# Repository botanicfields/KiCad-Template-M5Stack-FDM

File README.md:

# KiCad-Template-M5Stack-FDM
a PCB template of FDM-modules of M5Stack with footprints for KiCad.
## for KiCad 6
https://github.com/botanicfields/KiCad6-Environment

## for KiCad 5
- FDM: Fused Deposition Modeling
- Manufacture with a thickness of 1.0 mm.
- M-BUS pin numbers match pin headers and pin sockets in the KiCad library.
- The template has a notch, but it may be actually needed only for the M5Stack controller board.

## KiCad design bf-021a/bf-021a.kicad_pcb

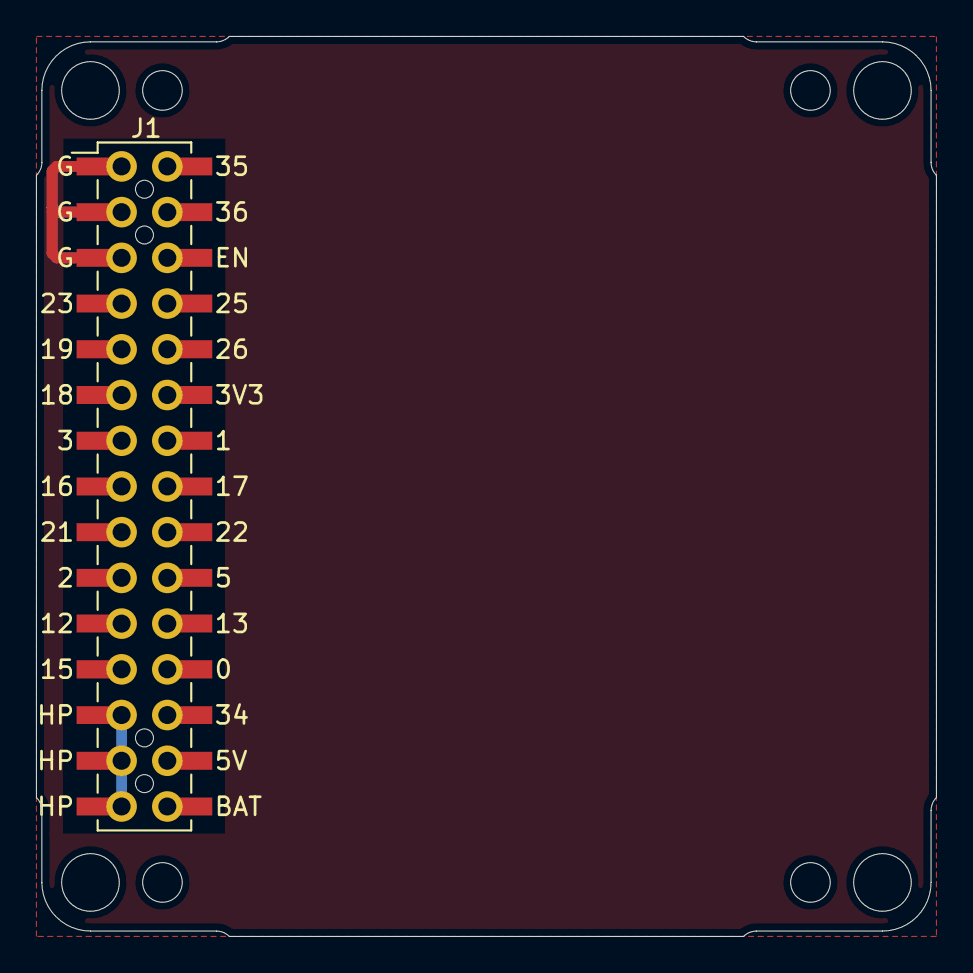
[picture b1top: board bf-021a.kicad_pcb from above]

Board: 2 copper layers, 50.0 x 50.0 mm, 9 parts (0 on the bottom side), 2 nets.

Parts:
H1, H2, H3, H4: MountingHole; BF@MountingHole_3.2mm_M3
H5, H6, H7, H8: MountingHole; BF@MountingHole_2.2mm_M2
J1: M-BUS; BF@M5Stack_MBUS

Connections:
GND: J1.2, J1.4, J1.6
VBUS: J1.26, J1.28, J1.30

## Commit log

2022-02-05 new
    new
2022-10-22 Update README.md
    link to KiCad6

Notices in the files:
bf-021a/bf-021a.kicad_pcb:
Copyright 2022 BotanicFields, Inc.
